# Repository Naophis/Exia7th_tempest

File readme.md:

# Exia7th_tempest

Exiaシリーズ７機目の機体。個体名`tempest`。（大会ではどちらで登録するかは不明）

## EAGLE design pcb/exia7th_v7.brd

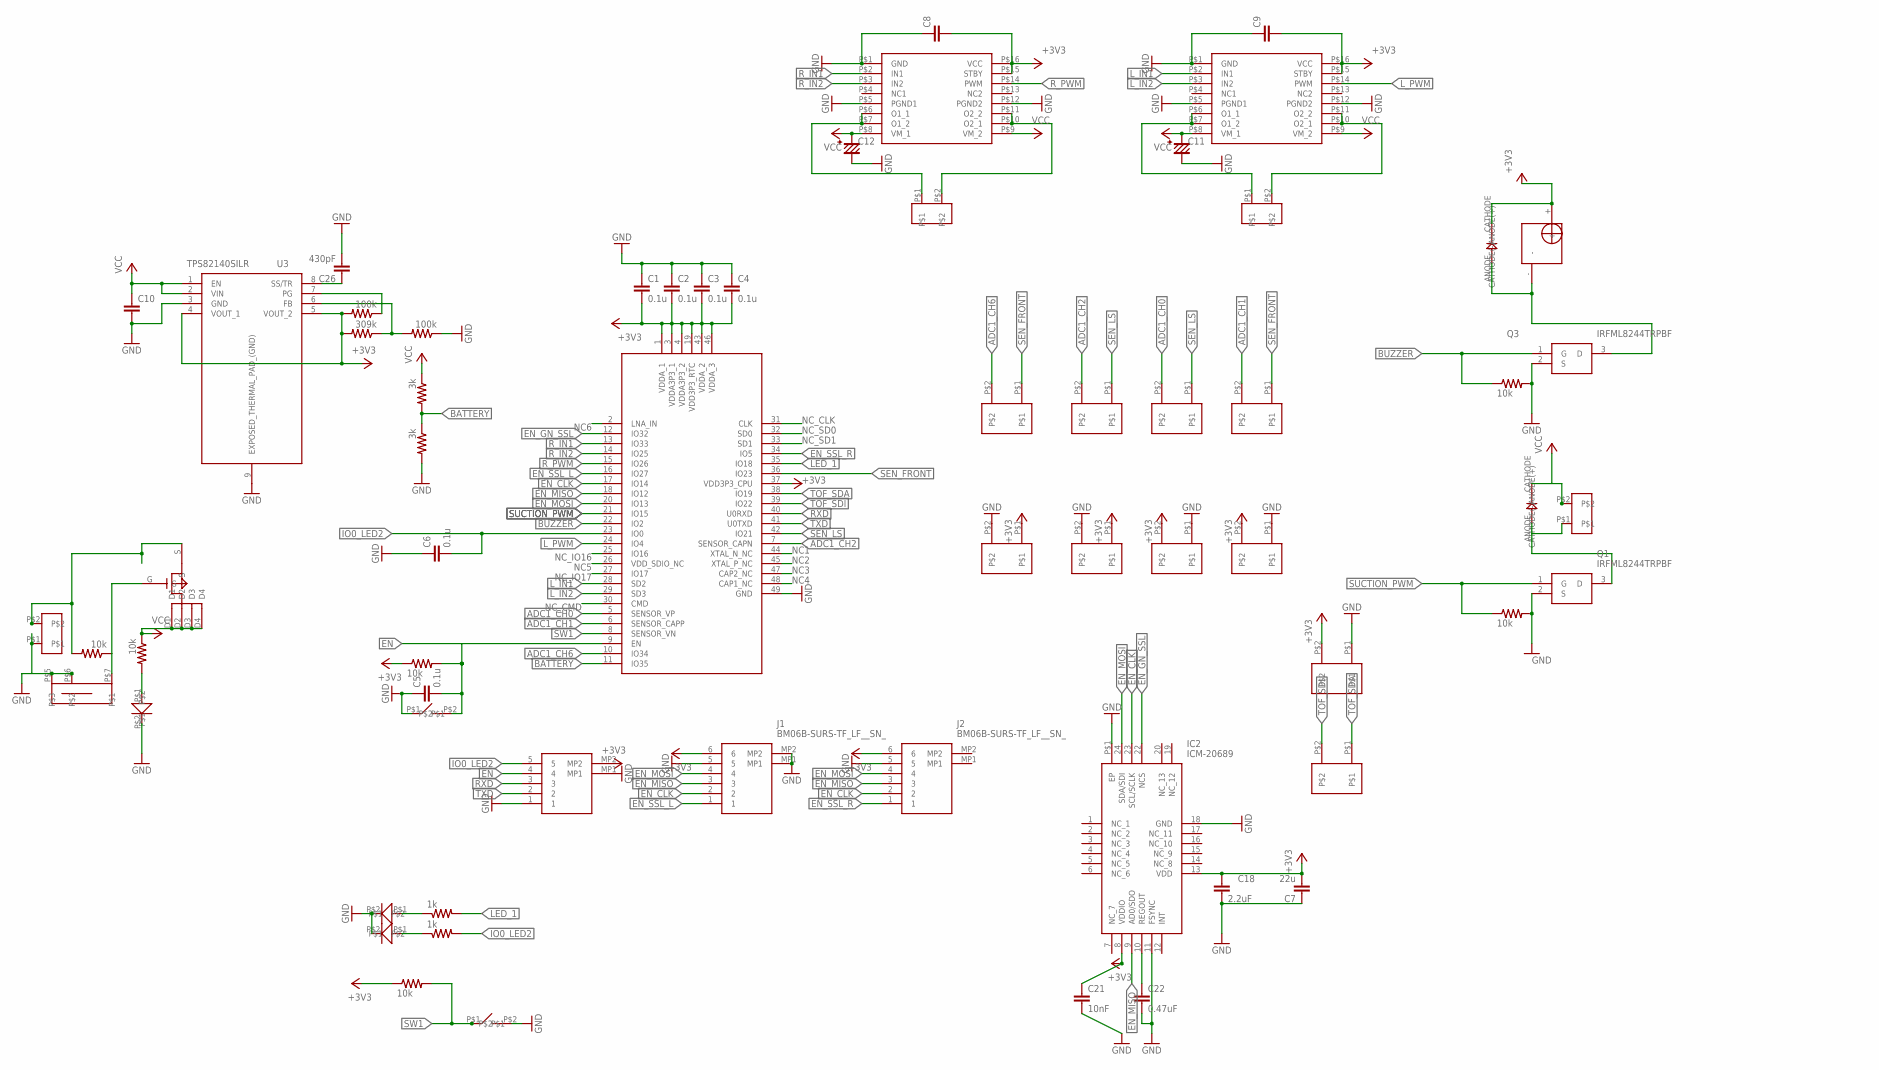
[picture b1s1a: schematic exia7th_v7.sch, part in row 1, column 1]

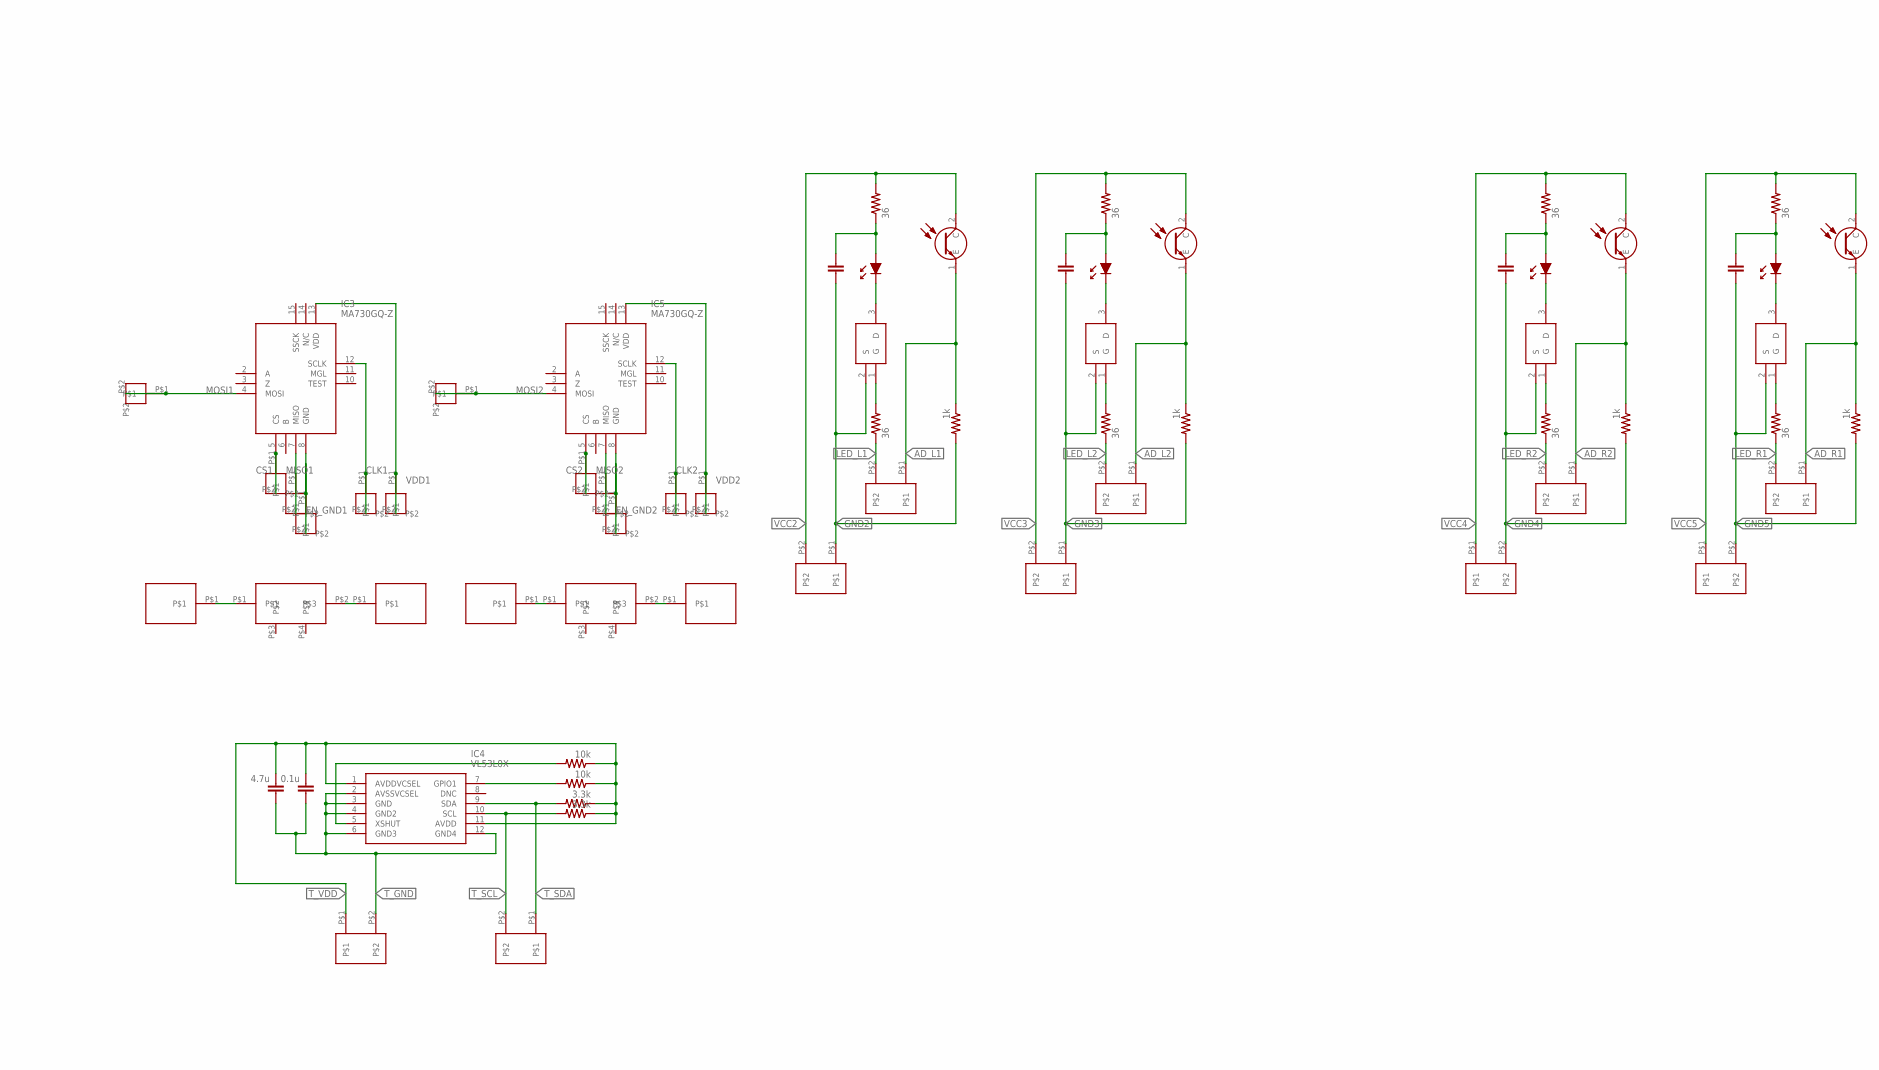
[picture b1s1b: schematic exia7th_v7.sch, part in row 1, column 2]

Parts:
C1, C2, C3, C4, C5, C6, C17: 0.1u; R1005
C7: 22u; C1608
C8, C9: C1005; R1005
C10: C1608
C11, C12: EC1
C13, C14, C15, C16: C3216
C18: 2.2uF; R1005
C19: 4.7u; R1005
C21: 10nF; R1005
C22: 0.47uF; R1005
C26: 430pF; R1005
IC1: ESP32-PICO-D4; ESP32-PICO-D4_1
IC2: ICM-20689; QFN50P400X400X95-25N
IC3, IC5: MA730GQ-Z; QFN50P300X300X100-17N
IC4: VL53L0X
J1, J2: BM06B-SURS-TF_LF__SN_; BM06BSURSTFLFSN
J3: BM05B-SURS-TF; BM05BSURSTF
Q1, Q3, Q4, Q6, Q8, Q10: IRFML8244TRPBF; SOT95P237X112-3N
Q2, Q5, Q7, Q9: LTR-4206E; LTR4206E
R1, R4, R7, R8, R9, R10, R22, R26: 10k; R1005
R2, R3: 3k; R1005
R5, R11, R12, R13, R15, R17, R18, R19: 36; R1005
R6, R14, R16, R23, R24, R54: 1k; R1005
R20, R21: 3.3k; R1005
R25, R36: 100k; R1005
R28: 309k; R1005
U3: TPS82140SILR; SIL0008D
U$1, U$19: TB6614
U$2, U$25, U$26: LED_1005
U$3, U$14, U$17, U$18: CONNECTOR_15_2; CONNECTOR_2
U$4, U$16: DCX6
U$5, U$6, U$7, U$8, U$9, U$10, U$11, U$20, U$21, U$32, U$34, U$35, U$45, U$46, U$48, U$49, U$50, U$51, U$61, U$62: SENSOR_FRONT1
U$12, U$15: DIODE
U$13: BUZZER_44; BUZZER
U$22, U$43: TVAF06
U$23: SI3493; MOS_FET_P
U$24, U$27, U$28, U$29, U$30, U$31, U$36, U$37, U$38, U$39, U$40, U$41: ENCORDER_PAD
U$33, U$42, U$44, U$47: SFH4550; SFH_4550
U$52, U$54, U$55, U$56: PAD
U$53: SWICH; SWITCH

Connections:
+3V3: C1.P$2 (2), C2.P$2 (2), C3.P$2 (2), C4.P$2 (2), C7.2, C8.P$2 (2), C9.P$2 (2), C18.P$1 (1), C21.P$1 (1), IC1.1 (VDDA_1), IC1.3 (VDDA3P3_1), IC1.4 (VDDA3P3_2), IC1.19 (VDD3P3_RTC), IC1.37 (VDD3P3_CPU), IC1.43 (VDDA_2), IC1.46 (VDDA_3), IC2.8 (VDDIO), IC2.13 (VDD), J1.6, J2.6, J3.MP2, R1.P$1 (1), R8.P$1 (1), R25.P$2 (2), R28.P$2 (2), U3.4 (VOUT_1), U3.5 (VOUT_2), U$1.P$15 (STBY), U$1.P$16 (VCC), U$7.P$1, U$10.P$2, U$11.P$2, U$13.+, U$15.CATHODE (CATHODE(-)), U$19.P$15 (STBY), U$19.P$16 (VCC), U$20.P$2, U$61.P$1
ADC1_CH0: IC1.5 (SENSOR_VP), U$9.P$2
ADC1_CH1: IC1.6 (SENSOR_CAPP), U$6.P$2
ADC1_CH2: IC1.7 (SENSOR_CAPN), U$8.P$2
ADC1_CH6: IC1.10 (IO34), U$5.P$2
AD_L1: Q2.1 (E), R54.P$1 (1), U$62.P$1
AD_L2: Q5.1 (E), R6.P$1 (1), U$35.P$1
AD_R1: Q9.1 (E), R16.P$1 (1), U$49.P$1
AD_R2: Q7.1 (E), R14.P$1 (1), U$46.P$1
BATTERY: IC1.11 (IO35), R2.P$2 (2), R3.P$1 (1)
BUZZER: IC1.22 (IO2), Q3.1 (G), R9.P$1 (1)
CLK1: IC3.12 (SCLK), U$30.P$1, U$30.P$2
CLK2: IC5.12 (SCLK), U$40.P$1, U$40.P$2
CS1: IC3.5 (CS), U$27.P$1, U$27.P$2
CS2: IC5.5 (CS), U$37.P$1, U$37.P$2
EN: C5.P$2 (2), IC1.9 (EN), J3.4, R1.P$2 (2), U$22.P$2
EN_CLK: IC1.17 (IO14), IC2.23 (SCL/SCLK), J1.2, J2.2
EN_GND1: IC3.8 (GND), U$29.P$1, U$29.P$2
EN_GND2: IC5.8 (GND), U$39.P$1, U$39.P$2
EN_GN_SSL: IC1.12 (IO32), IC2.22 (NCS)
EN_MISO: IC1.18 (IO12), IC2.9 (AD0/SDO), J1.3, J2.3
EN_MOSI: IC1.20 (IO13), IC2.24 (SDA/SDI), J1.4, J2.4
EN_SSL_L: IC1.16 (IO27), J1.1
EN_SSL_R: IC1.34 (IO5), J2.1
GND: C1.P$1 (1), C2.P$1 (1), C3.P$1 (1), C4.P$1 (1), C5.P$1 (1), C6.P$1 (1), C7.1, C8.P$1 (1), C9.P$1 (1), C10.2, C11.2, C12.2, C18.P$2 (2), C21.P$2 (2), C22.P$2 (2), C26.P$2 (2), IC1.49 (GND), IC2.11 (FSYNC), IC2.18 (GND), IC2.P$1 (EP), J1.5, J1.MP1, J1.MP2, J2.5, J3.1, J3.MP1, Q1.2 (S), Q3.2 (S), R3.P$2 (2), R9.P$2 (2), R10.P$2 (2), R36.P$1 (1), U3.3 (GND), U3.9 (EXPOSED_THERMAL_PAD_(GND)), U$1.P$1 (GND), U$1.P$5 (PGND1), U$1.P$12 (PGND2), U$2.P$2, U$3.P$1, U$7.P$2, U$10.P$1, U$11.P$1, U$19.P$1 (GND), U$19.P$5 (PGND1), U$19.P$12 (PGND2), U$20.P$1, U$22.P$1, U$25.P$2, U$26.P$2, U$43.P$2, U$53.P$5, U$53.P$6, U$61.P$2
GND2: C13.2, Q4.2 (S), R54.P$2 (2), U$32.P$1
GND3: C14.2, Q6.2 (S), R6.P$2 (2), U$34.P$1
GND4: C15.2, Q8.2 (S), R14.P$2 (2), U$45.P$2
GND5: C16.2, Q10.2 (S), R16.P$2 (2), U$48.P$2
IO0_LED2: C6.P$2 (2), IC1.23 (IO0), J3.5, R23.P$2 (2)
LED_1: IC1.35 (IO18), R24.P$2 (2)
LED_L1: R5.P$1 (1), U$62.P$2
LED_L2: R11.P$1 (1), U$35.P$2
LED_R1: R17.P$1 (1), U$49.P$2
LED_R2: R15.P$1 (1), U$46.P$2
L_IN1: IC1.28 (SD2), U$1.P$2 (IN1)
L_IN2: IC1.29 (SD3), U$1.P$3 (IN2)
L_PWM: IC1.24 (IO4), U$1.P$14 (PWM)
MISO1: IC3.7 (MISO), U$28.P$1, U$28.P$2
MISO2: IC5.7 (MISO), U$38.P$1, U$38.P$2
MOSI1: IC3.4 (MOSI), U$24.P$1, U$24.P$2
MOSI2: IC5.4 (MOSI), U$36.P$1, U$36.P$2
unnamed: U$17.P$1, U$19.P$6 (O1_1), U$19.P$7 (O1_2)
unnamed: U$17.P$2, U$19.P$10 (O2_1), U$19.P$11 (O2_2)
unnamed: Q3.3 (D), U$13.-, U$15.ANODE (ANODE(+))
unnamed: R4.P$2 (2), U$2.P$1
unnamed: C22.P$1 (1), IC2.10 (REGOUT)
unnamed: Q4.3 (D), U$44.CASODE (K)
unnamed: Q4.1 (G), R5.P$2 (2)
unnamed: C14.1, R13.P$1 (1), U$33.ANODE (A)
unnamed: U$1.P$6 (O1_1), U$1.P$7 (O1_2), U$18.P$1
unnamed: U$1.P$10 (O2_1), U$1.P$11 (O2_2), U$18.P$2
unnamed: Q6.3 (D), U$33.CASODE (K)
unnamed: Q6.1 (G), R11.P$2 (2)
unnamed: C15.1, R18.P$1 (1), U$42.ANODE (A)
unnamed: Q8.3 (D), U$42.CASODE (K)
unnamed: R7.P$1 (1), U$23.G, U$53.P$7
unnamed: Q8.1 (G), R15.P$2 (2)
unnamed: R7.P$2 (2), U$3.P$2, U$23.S
unnamed: C16.1, R19.P$1 (1), U$47.ANODE (A)
unnamed: Q10.3 (D), U$47.CASODE (K)
unnamed: Q10.1 (G), R17.P$2 (2)
unnamed: IC4.5 (XSHUT), R22.P$2 (2)
unnamed: IC4.7 (GPIO1), R26.P$2 (2)
unnamed: U$4.P$1, U$52.P$1
unnamed: U$4.P$2, U$54.P$1
unnamed: U$16.P$1, U$55.P$1
unnamed: C26.P$1 (1), U3.8 (SS/TR)
unnamed: U$16.P$2, U$56.P$1
unnamed: R28.P$1 (1), R36.P$2 (2), U3.6 (FB)
unnamed: R25.P$1 (1), U3.7 (PG)
unnamed: R23.P$1 (1), U$26.P$1
unnamed: R24.P$1 (1), U$25.P$1
unnamed: C13.1, R12.P$1 (1), U$44.ANODE (A)
unnamed: Q1.3 (D), U$12.ANODE (ANODE(+)), U$14.P$1
NC1: IC1.44 (XTAL_N_NC)
NC2: IC1.45 (XTAL_P_NC)
NC3: IC1.47 (CAP2_NC)
NC4: IC1.48 (CAP1_NC)
NC5: IC1.26 (VDD_SDIO_NC)
NC6: IC1.2 (LNA_IN)
NC_CLK: IC1.31 (CLK)
NC_CMD: IC1.30 (CMD)
NC_IO16: IC1.25 (IO16)
NC_IO17: IC1.27 (IO17)
NC_SD0: IC1.32 (SD0)
NC_SD1: IC1.33 (SD1)
RXD: IC1.40 (U0RXD), J3.3
R_IN1: IC1.13 (IO33), U$19.P$2 (IN1)
R_IN2: IC1.14 (IO25), U$19.P$3 (IN2)
R_PWM: IC1.15 (IO26), U$19.P$14 (PWM)
SEN_FRONT: IC1.36 (IO23), U$5.P$1, U$6.P$1
SEN_LS: IC1.42 (IO21), U$8.P$1, U$9.P$1
SUCTION_PWM: IC1.21 (IO15), Q1.1 (G), R10.P$1 (1)
SW1: IC1.8 (SENSOR_VN), R8.P$2 (2), U$43.P$1
TOF_SDA: IC1.38 (IO19), U$21.P$1
TOF_SDI: IC1.39 (IO22), U$21.P$2
TXD: IC1.41 (U0TXD), J3.2
T_GND: C17.P$1 (1), C19.P$1 (1), IC4.2 (AVSSVCSEL), IC4.3 (GND), IC4.4 (GND2), IC4.6 (GND3), IC4.12 (GND4), U$50.P$2
T_SCL: IC4.10 (SCL), R21.P$2 (2), U$51.P$2
T_SDA: IC4.9 (SDA), R20.P$2 (2), U$51.P$1
T_VDD: C17.P$2 (2), C19.P$2 (2), IC4.1 (AVDDVCSEL), IC4.11 (AVDD), R20.P$1 (1), R21.P$1 (1), R22.P$1 (1), R26.P$1 (1), U$50.P$1
VCC: C10.1, C11.1 (PLUS), C12.1 (PLUS), R2.P$1 (1), R4.P$1 (1), U3.1 (EN), U3.2 (VIN), U$1.P$8 (VM_1), U$1.P$9 (VM_2), U$12.CATHODE (CATHODE(-)), U$14.P$2, U$19.P$8 (VM_1), U$19.P$9 (VM_2), U$23.D1, U$23.D2, U$23.D3, U$23.D4
VCC2: Q2.2 (C), R12.P$2 (2), U$32.P$2
VCC3: Q5.2 (C), R13.P$2 (2), U$34.P$2
VCC4: Q7.2 (C), R18.P$2 (2), U$45.P$1
VCC5: Q9.2 (C), R19.P$2 (2), U$48.P$1
VDD1: IC3.13 (VDD), U$31.P$1, U$31.P$2
VDD2: IC5.13 (VDD), U$41.P$1, U$41.P$2

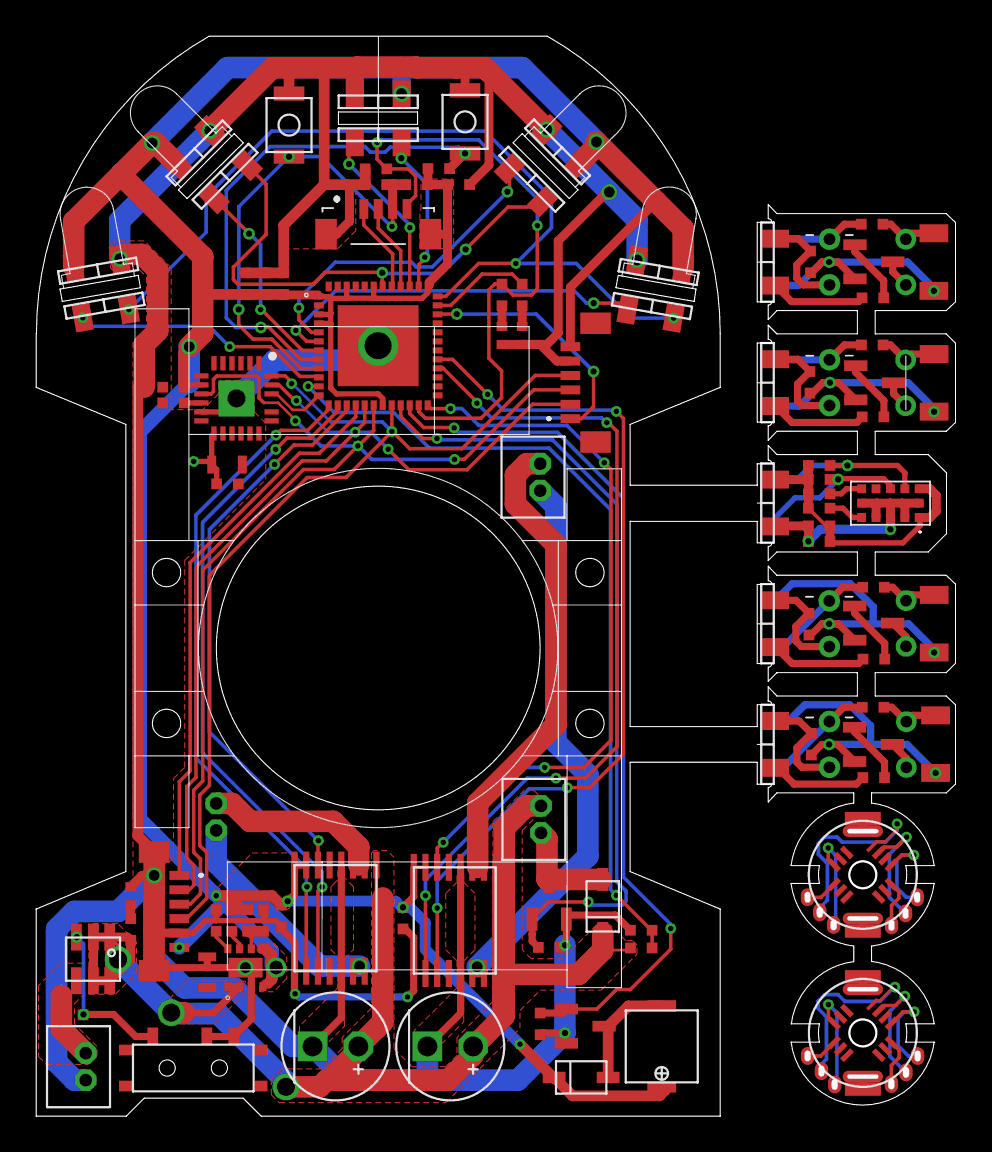
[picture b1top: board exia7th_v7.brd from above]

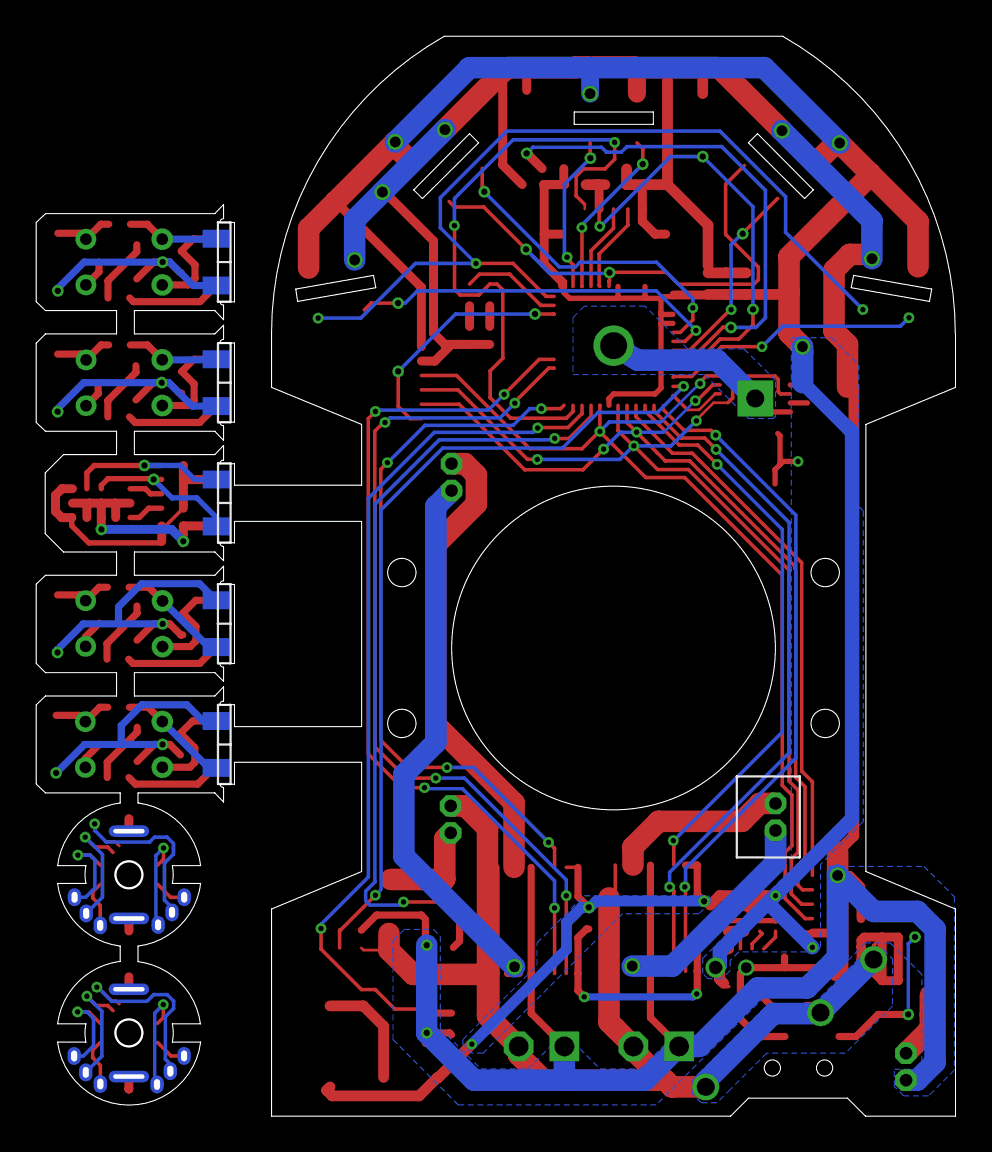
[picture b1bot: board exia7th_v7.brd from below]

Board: 2 copper layers, 51.1 x 60.0 mm, 128 parts (6 on the bottom side), 97 nets.

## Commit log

2021-04-24 Create LICENSE
2021-04-25 add module
2021-05-02 update moudle
